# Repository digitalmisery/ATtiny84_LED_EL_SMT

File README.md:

ATtiny84 LED + EL (SMT)
=======================
This is a miniaturized version of my other [ATtiny84 LED + EL](http://github.com/digitalmisery/ATtiny84_LED_EL)
board. It uses mainly surface-mount components which allowed me to shrink it down to 1.0" x 1.0".
This is the version that ultimately made it into my [Valentine Love Light](http://www.digitalmisery.com/projects/valentines-day/valentine-love-light/).

The PCB is shared on [OSH Park](http://oshpark.com/shared_projects/lLCQlTCR).

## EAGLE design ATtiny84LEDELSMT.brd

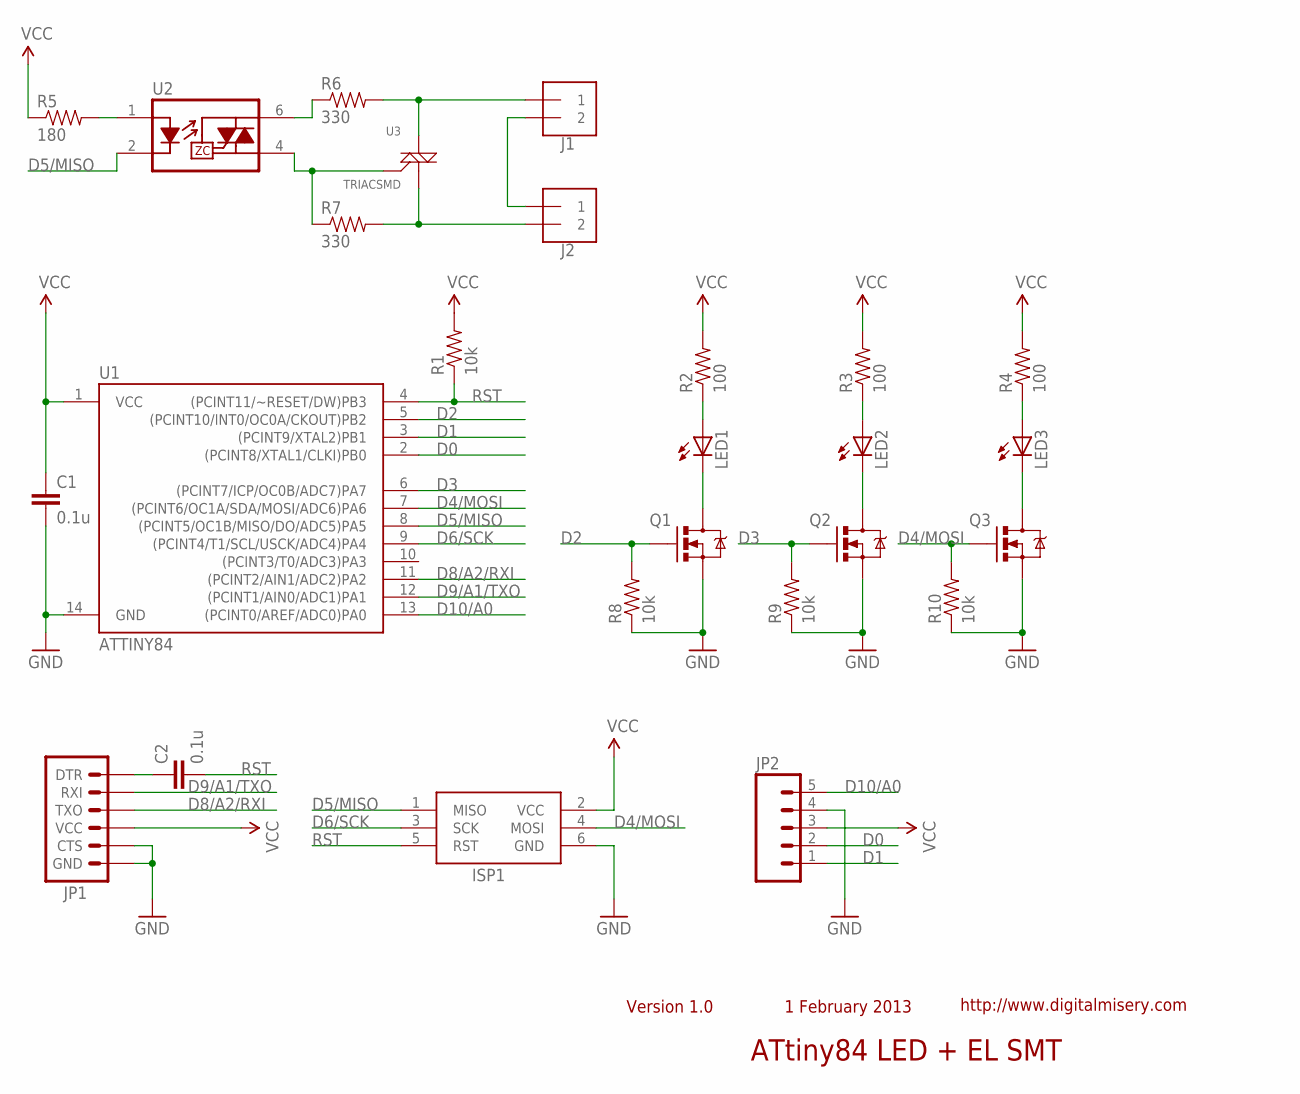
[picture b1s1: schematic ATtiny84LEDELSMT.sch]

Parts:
C1, C2: 0.1u; 0805
ISP1: AVRISP-6; AVRISP
J1, J2: 1X2-3.5MM
JP1: ARDUINO_SERIAL_PROGRAMPTH; 1X06
JP2: M05PTH; 1X05
LED1, LED2, LED3: LED5MM
Q1, Q2, Q3: MOSFET-NCHANNELBSS138; SOT23
R1, R8, R9, R10: 10k; 0805
R2, R3, R4: 100; 0805
R5: 180; 0805
R6, R7: 330; 0805
U1: ATTINY84; SO14
U2: MOC3063S; DIP8SMD
U3: TRIACSMD; SOT223

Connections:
D0: JP2.2, U1.2 ((PCINT8/XTAL1/CLKI)PB0)
D1: JP2.1, U1.3 ((PCINT9/XTAL2)PB1)
D2: Q1.1 (G), R8.2, U1.5 ((PCINT10/INT0/OC0A/CKOUT)PB2)
D3: Q2.1 (G), R9.2, U1.6 ((PCINT7/ICP/OC0B/ADC7)PA7)
D4/MOSI: ISP1.4 (MOSI), Q3.1 (G), R10.2, U1.7 ((PCINT6/OC1A/SDA/MOSI/ADC6)PA6)
D5/MISO: ISP1.1 (MISO), U1.8 ((PCINT5/OC1B/MISO/DO/ADC5)PA5), U2.2 (K)
D6/SCK: ISP1.3 (SCK), U1.9 ((PCINT4/T1/SCL/USCK/ADC4)PA4)
D8/A2/RXI: JP1.3 (TXO), U1.11 ((PCINT2/AIN1/ADC2)PA2)
D9/A1/TXO: JP1.2 (RXI), U1.12 ((PCINT1/AIN0/ADC1)PA1)
D10/A0: JP2.5, U1.13 ((PCINT0/AREF/ADC0)PA0)
GND: C1.2, ISP1.6 (GND), JP1.5 (CTS), JP1.6 (GND), JP2.4, Q1.2 (S), Q2.2 (S), Q3.2 (S), R8.1, R9.1, R10.1, U1.14 (GND)
unnamed: C2.1, JP1.1 (DTR)
unnamed: R5.2, U2.1 (A)
unnamed: LED1.K (C), Q1.3 (D)
unnamed: LED2.K (C), Q2.3 (D)
unnamed: R6.1, U2.6 (T1)
unnamed: LED3.K (C), Q3.3 (D)
unnamed: R7.1, U2.4 (T2), U3.3 (G)
unnamed: LED1.A, R2.1
unnamed: J1.2, J2.1
unnamed: LED2.A, R3.1
unnamed: J2.2, R7.2, U3.1 (M1)
unnamed: LED3.A, R4.1
unnamed: J1.1, R6.2, U3.2 (M2)
RST: C2.2, ISP1.5 (RST), R1.1, U1.4 ((PCINT11/~RESET/DW)PB3)
VCC: C1.1, ISP1.2 (VCC), JP1.4 (VCC), JP2.3, R1.2, R2.2, R3.2, R4.2, R5.1, U1.1 (VCC)

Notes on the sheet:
http://www.digitalmisery.com
1 February 2013
Version 1.0
ATtiny84 LED + EL SMT

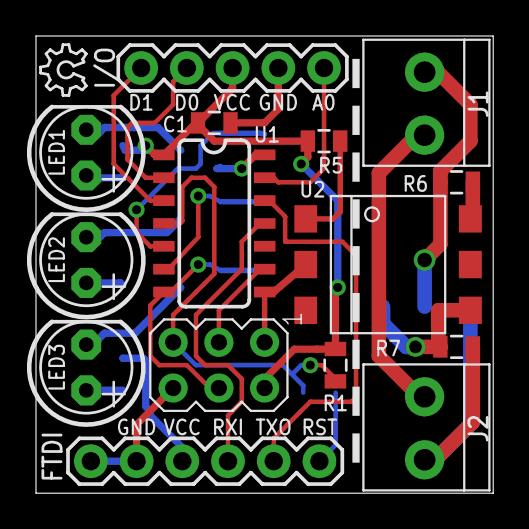
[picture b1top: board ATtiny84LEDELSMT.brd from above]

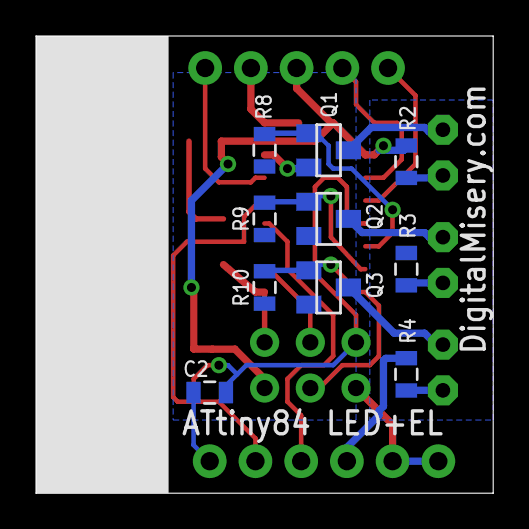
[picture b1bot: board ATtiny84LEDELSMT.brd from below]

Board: 2 copper layers, 25.4 x 25.4 mm, 27 parts (11 on the bottom side), 26 nets.

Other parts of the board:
U$2: OSHW_6X100_NOTEXT

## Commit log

2013-08-01 Added Eagle PCB design files.
2014-01-12 Added pictures
2014-01-12 Added link to OSH Park.

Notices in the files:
parts and their libraries:
SparkFun-DigitalIC: Licensing: CC v3.0 Share-Alike You are welcome to use this library for commercial purposes.
